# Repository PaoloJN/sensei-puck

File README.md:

# Sensei Puck

**Archived 2026-10-24. Never built.** This is the record of a college
proof-of-concept that got as far as a finished schematic, a mostly routed
4-layer PCB and a bring-up firmware variant, then stopped before the first
board order. It is kept public as a design record, not as a kit to build.

## What it was supposed to be

A Ø46 mm disc you drop into a glass or plastic jug. It sits on the bottom,
fully submerged, and logs what happens to the water: conductivity, temperature,
pressure (fill level and movement), a small spectral sensor with white / IR / UV
illumination, a capacitive wetness pair and a microphone. An nRF52840 module
talks BLE to a phone, radiating down through the container base from a dry air
cavity. Clear epoxy dip for waterproofing, magnetic pads for charging, OTA DFU
as the only reflash path after the dip. Raw counts plus acquisition settings
are stored; calibration happens downstream.

It was never meant to assess whether water is safe to drink. The honest scope
was "has this water changed since I last looked, and roughly how".

## What exists

| Part | State |
|---|---|
| `hardware/sensei-puck/` | KiCad 10 project. Schematic complete, ERC clean. Board placed on both faces (139 footprints, 4 layers). Last check: 1 clearance error, 25 connections still unrouted around the module. |
| `hardware/board-spec.md` | Pin contract, power rules, sensor notes, release requirements. |
| `firmware/` | PlatformIO + Adafruit nRF52 core. Custom `mdbt50q_puck` board and variant, safe-start `initVariant()`, REGOUT0 guard, a commissioning idle image and XIAO bench sketches. All targets compile. Nothing was ever flashed to a carrier. |
| `docs/images/` | Board renders, concept render, app mock (see the gallery below). |

Key parts: Raytac MDBT50Q-1MV2 (nRF52840), MCP73832 charger, TPS61023 5 V
boost for a 12-LED ring, FDC1004 capacitance, MS5837 pressure, AS7341 spectral,
LSM6DSO IMU, IM69D130 PDM mic, DS18B20U+ temperature, gold ENIG electrodes for
a 4-wire AC conductivity cell driven straight from GPIO with two-resistor
auto-ranging.

## Why it stopped

None of these alone killed it. Together they did.

- **A sealed puck is unforgiving.** Epoxy dip means no repair and no SWD after
  sealing, so the custom bootloader and the OTA path had to be proven perfect
  before the first dip. On a ~$300 budget with two PCB spins, one mistake in
  the pin map or the charger ends the project.
- **Radio through water was an unverified bet.** 2.4 GHz does not go through
  water. The plan relied on an air cavity under the board and the container
  base being thin glass or plastic, with store-and-forward and a tilt-triggered
  sync to cover the gaps. Plausible on paper, never measured, and it rules out
  metal bottles and thick ceramics outright.
- **The layout never closed.** The 0.4 mm pad pitch on the module, the no-via
  zone under the capacitive electrodes and the antenna keep-out box the module
  in on a 46 mm disc. Five autorouting strategies, two pin-swap passes and a
  0.1 mm local rule area got it from 130 opens to 25. The rest needed a
  placement redesign or a third attempt.
- **Every number needs a reference.** Conductivity and temperature readings
  only mean something against KCl standards or a lab meter. That is a bench
  campaign the project did not have time or access for.
- **The market check.** Products like WaterH (sensor in its own bottle) and the
  pool floats already ship the idea where it works, by owning the container.
  A drop-in puck for any container is the hard version, and the gap in the
  market is smaller than it looked.

## What I'd keep from it

The symmetric sensor face with the electrodes as the visual, the
GPIO-driven AC conductivity cell with switched bias, the "store raw counts and
settings" rule, and the habit of writing down every decision with a date and a
reason. The full decision log, work log, research notes and the earlier v1
board are in the git history before the archive commit.

## Gallery

## Running the firmware

```sh
cd firmware
pio run -e mdbt50q_puck -e puck
```

`mdbt50q_puck` is the carrier target. `puck` and `bench_*` run on a Seeed XIAO
nRF52840 Sense, which was the bench mule. See `firmware/README.md`.

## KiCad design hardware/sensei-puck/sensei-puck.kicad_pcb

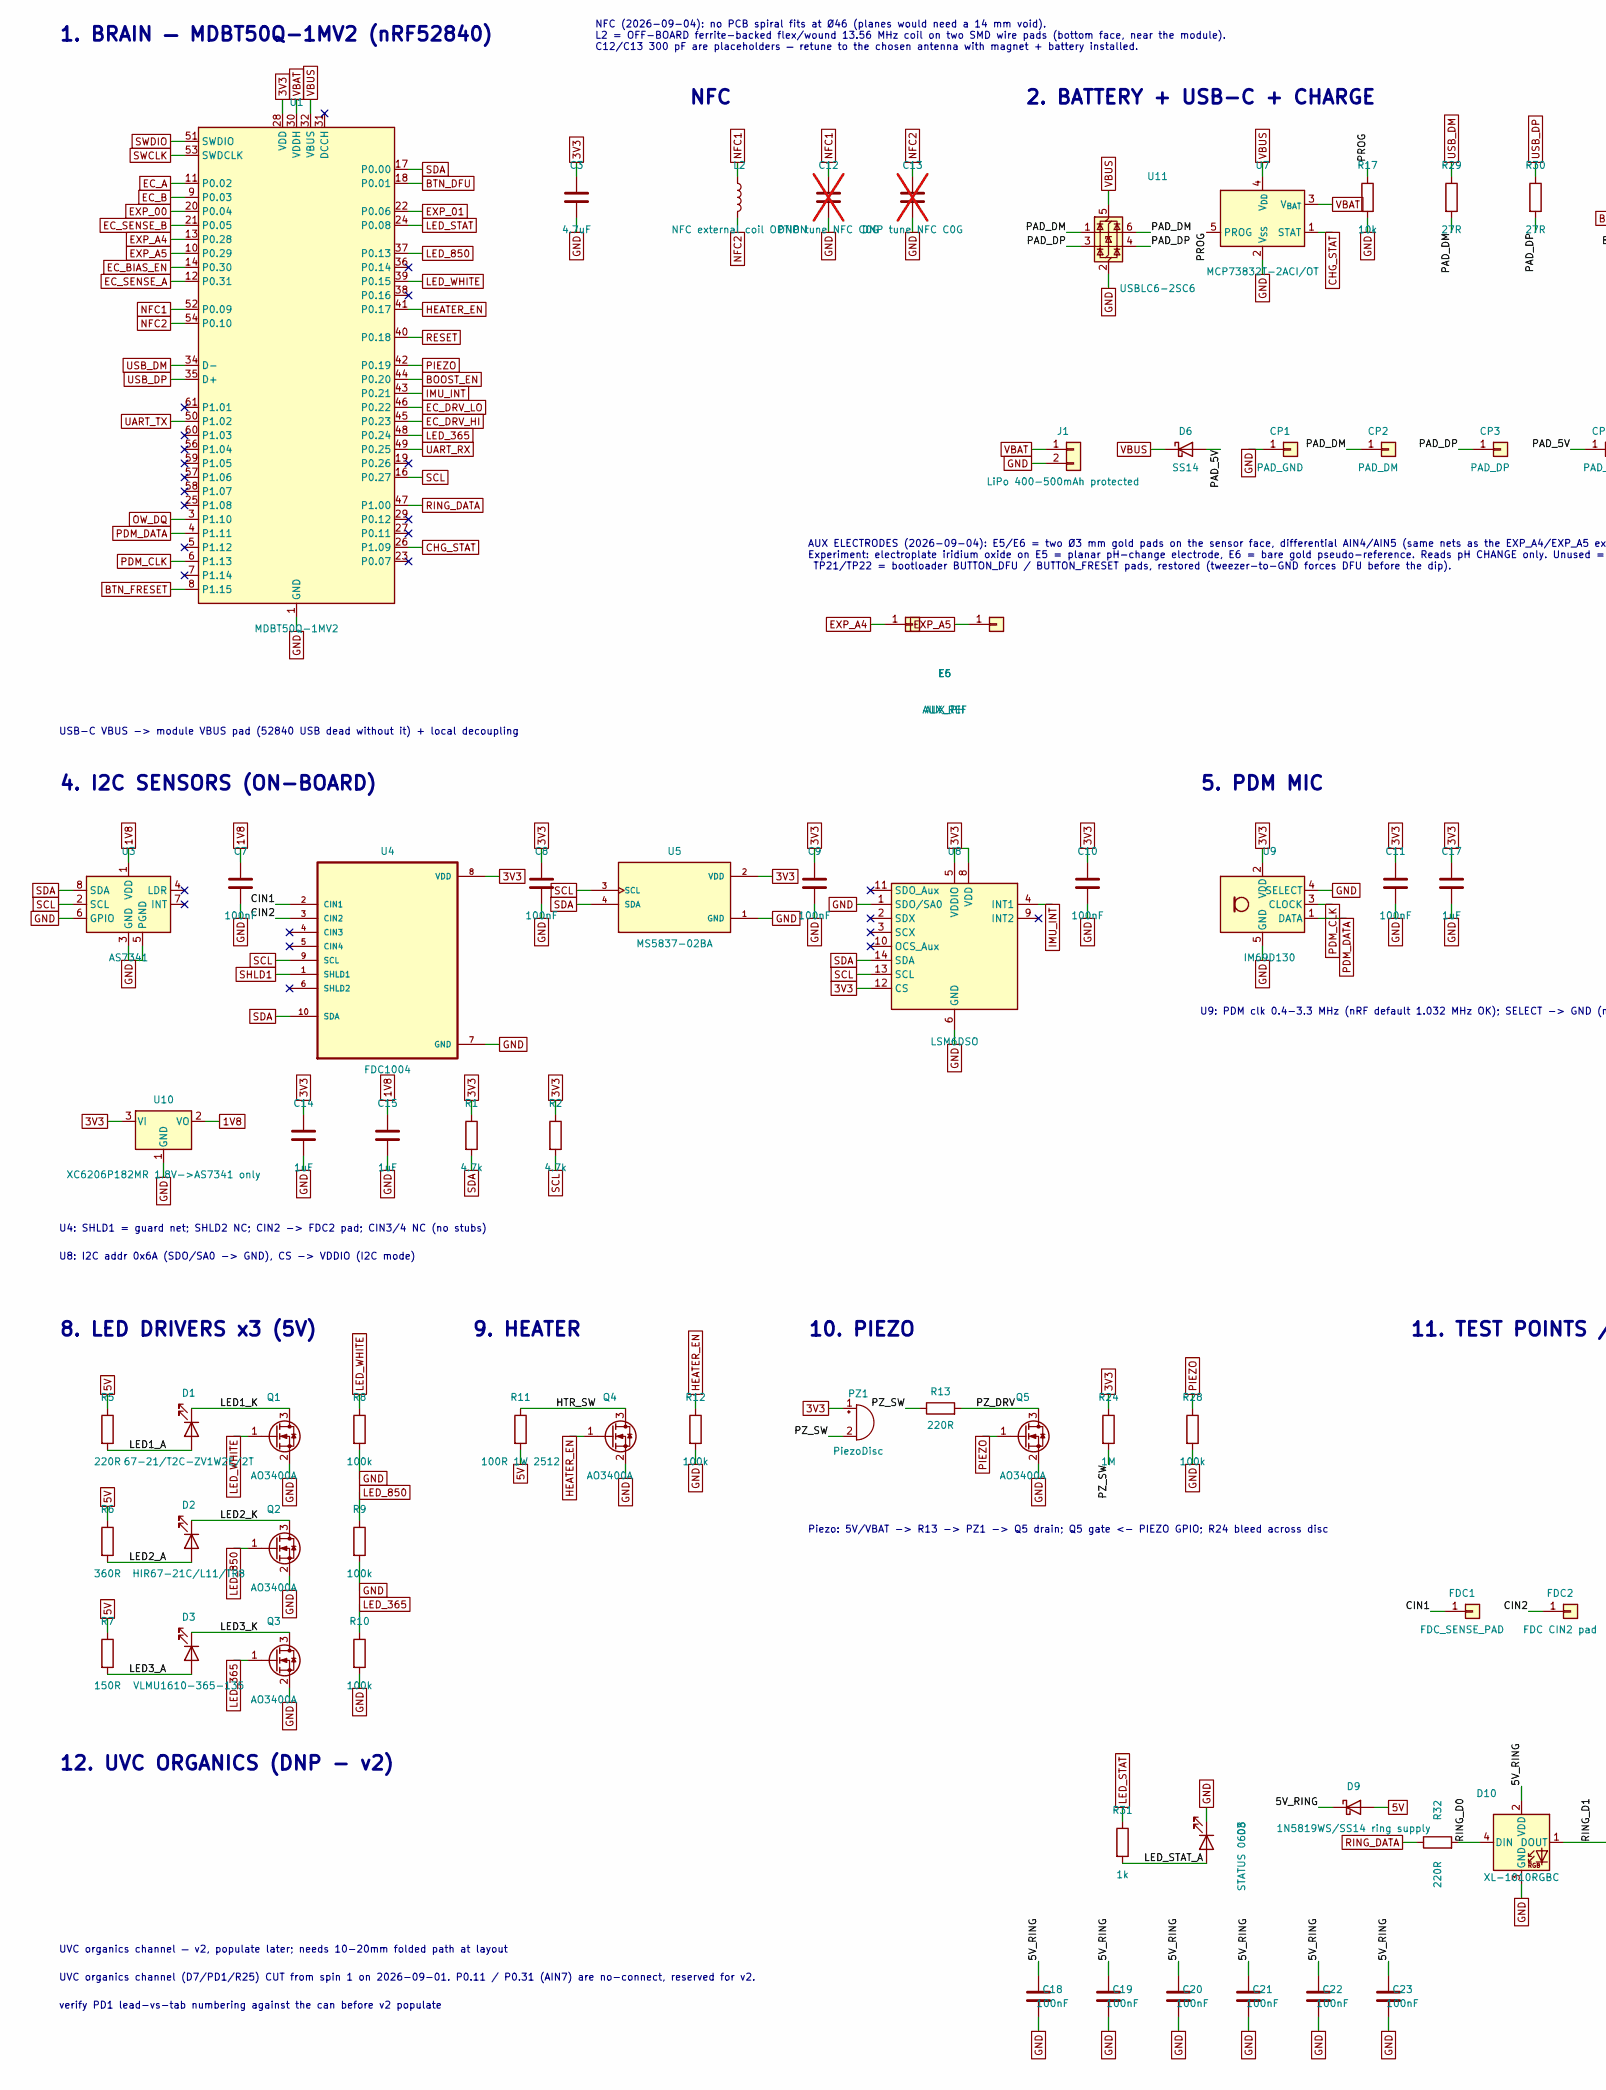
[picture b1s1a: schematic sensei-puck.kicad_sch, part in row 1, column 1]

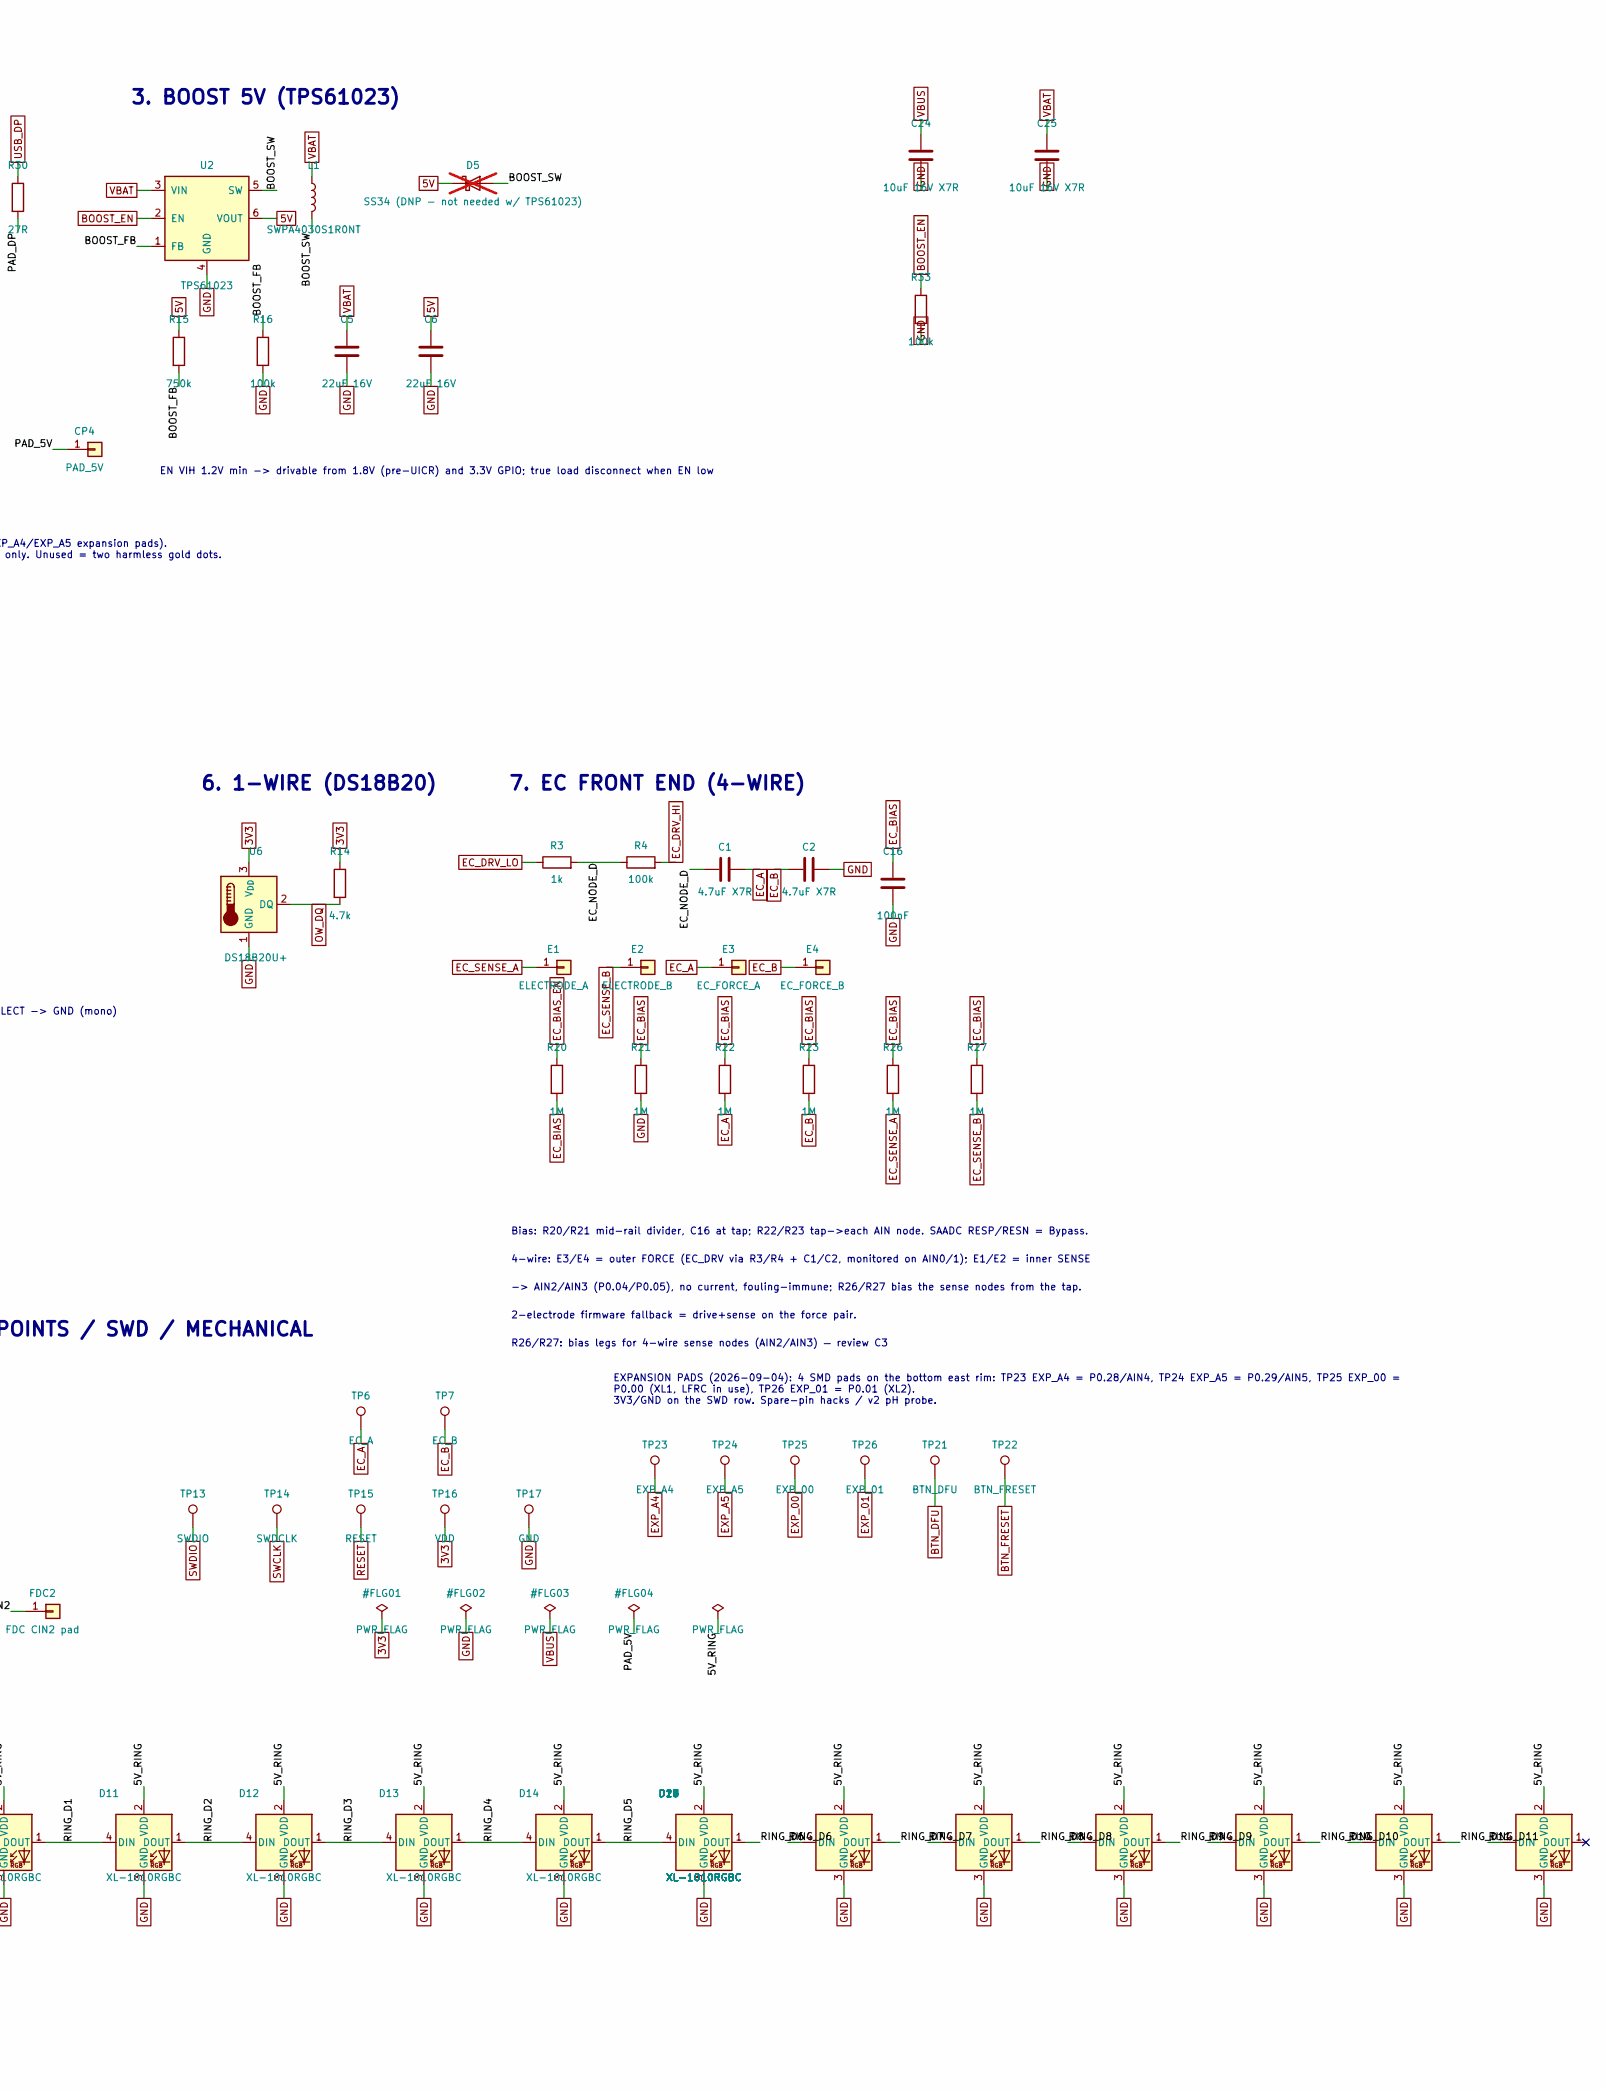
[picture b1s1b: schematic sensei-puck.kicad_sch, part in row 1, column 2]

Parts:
C1, C2: 4.7uF X7R; C_0805_2012Metric_Pad1.18x1.45mm_HandSolder
C3: 4.7uF; C_0805_2012Metric
C5, C6: 22uF 16V; C_0805_2012Metric_Pad1.18x1.45mm_HandSolder
C7, C8, C9, C10, C11, C16, C18, C19, C20, C21, C22, C23: 100nF; C_0402_1005Metric
C12, C13: DNP tune NFC C0G; C_0402_1005Metric; not fitted
C14, C15, C17: 1uF; C_0402_1005Metric
C24, C25: 10uF 16V X7R; C_1206_3216Metric
CP1: PAD_GND; CHG_Pad_D2.0mm
CP2: PAD_DM; CHG_Pad_D2.0mm
CP3: PAD_DP; CHG_Pad_D2.0mm
CP4: PAD_5V; CHG_Pad_D2.0mm
D1: 67-21/T2C-ZV1W2E/2T; LED_Everlight_67-21_PLCC2
D2: HIR67-21C/L11/TR8; LED_Everlight_67-21_PLCC2
D3: VLMU1610-365-135; LED_Vishay_VLMU1610
D5: SS34 (DNP - not needed w/ TPS61023); D_SMA; not fitted
D6: SS14; D_SOD-123
D8: STATUS 0603; LED_0603_1608Metric
D9: 1N5819WS/SS14 ring supply; D_SOD-123
D10, D11, D12, D13, D14, D15, D16, D17, D18, D19, D20, D21: XL-1010RGBC; LED_XL-1010RGBC
E1: ELECTRODE_A; EC_Electrode_2x8mm
E2: ELECTRODE_B; EC_Electrode_2x8mm
E3: EC_FORCE_A; EC_Electrode_2x8mm
E4: EC_FORCE_B; EC_Electrode_2x8mm
E5: AUX_PH; AUX_Pad_D3.0mm
E6: AUX_REF; AUX_Pad_D3.0mm
FDC1: FDC_SENSE_PAD; FDC_Sense_Pad_D7.9mm
FDC2: FDC CIN2 pad; FDC_Sense_Ring_D10-12.8mm
J1: LiPo 400-500mAh protected; JST_PH_S2B-PH-K_1x02_P2.00mm_Horizontal
L1: SWPA4030S1R0NT; L_Sunlord_SWPA4030S
L2: NFC external coil OPTION; WirePad_1x02_SMD_1.5x3mm
PZ1: PiezoDisc; PZ_WirePad_1x02_SMD
Q1, Q2, Q3, Q4, Q5: AO3400A; SOT-23
R1, R2, R14: 4.7k; R_0402_1005Metric
R3, R31: 1k; R_0402_1005Metric
R4, R8, R9, R10, R12, R16, R28, R33: 100k; R_0402_1005Metric
R5, R13, R32: 220R; R_0402_1005Metric
R6: 360R; R_0402_1005Metric
R7: 150R; R_0402_1005Metric
R11: 100R 1W 2512; R_2512_6332Metric_Pad1.40x3.35mm_HandSolder
R15: 750k; R_0402_1005Metric
R17: 10k; R_0402_1005Metric
R20, R21, R22, R23, R24, R26, R27: 1M; R_0402_1005Metric
R29, R30: 27R; R_0402_1005Metric
TP6: EC_A; TestPoint_Pad_D1.5mm
TP7: EC_B; TestPoint_Pad_D1.5mm
TP13: SWDIO; TestPoint_Pad_D1.5mm
TP14: SWDCLK; TestPoint_Pad_D1.5mm
TP15: RESET; TestPoint_Pad_D1.5mm
TP16: VDD; TestPoint_Pad_D1.5mm
TP17: GND; TestPoint_Pad_D1.5mm
TP21: BTN_DFU; ExpPad_1.2x2.2mm
TP22: BTN_FRESET; ExpPad_1.2x2.2mm
TP23: EXP_A4; ExpPad_1.2x2.2mm
TP24: EXP_A5; ExpPad_1.2x2.2mm
TP25: EXP_00; ExpPad_1.2x2.2mm
TP26: EXP_01; ExpPad_1.2x2.2mm
U1: MDBT50Q-1MV2
U2: TPS61023; SOT-563
U3: AS7341; AMS_OLGA-8_2x3.1mm_P0.8mm
U4: FDC1004; SOP50P490X110-10N
U5: MS5837-02BA; XDCR_MS583702BA01-50
U6: DS18B20U+; DS18B20U_MSOP8
U7: MCP73832T-2ACI/OT; SOT-23-5
U8: LSM6DSO; LGA-14_3x2.5mm_P0.5mm_LayoutBorder3x4y
U9: IM69D130; Infineon_PG-LLGA-5-1
U10: XC6206P182MR 1.8V->AS7341 only; SOT-23
U11: USBLC6-2SC6; SOT-23-6

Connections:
1V8: C7.1, C15.1, U3.1 (VDD), U10.2 (VO)
3V3: C3.1, C8.1, C9.1, C10.1, C11.1, C14.1, C17.1, PZ1.1 (+), R1.1, R2.1, R14.1, R24.1, TP16.1 (1_1), U1.28 (VDD), U4.8 (VDD), U5.2 (VDD), U6.3 (V_{DD}), U8.5 (VDDIO), U8.8 (VDD), U8.12 (CS), U9.2 (VDD), U10.3 (VI)
5V: C6.1, D5.1 (K), D9.2 (A), R5.1, R6.1, R7.1, R11.2, R15.1, U2.6 (VOUT)
/5V_RING: C18.1, C19.1, C20.1, C21.1, C22.1, C23.1, D9.1 (K), D10.2 (VDD), D11.2 (VDD), D12.2 (VDD), D13.2 (VDD), D14.2 (VDD), D15.2 (VDD), D16.2 (VDD), D17.2 (VDD), D18.2 (VDD), D19.2 (VDD), D20.2 (VDD), D21.2 (VDD)
/BOOST_FB: R15.2, R16.1, U2.1 (FB)
/BOOST_SW: D5.2 (A), L1.2, U2.5 (SW)
/CIN1: FDC1.1 (Pin_1_1), U4.2 (CIN1)
/CIN2: FDC2.1 (Pin_1_1), U4.3 (CIN2)
/EC_NODE_D: C1.1, R3.2, R4.1
/HTR_SW: Q4.3 (D), R11.1
/LED1_A: D1.2 (A), R5.2
/LED1_K: D1.1 (K), Q1.3 (D)
/LED2_A: D2.2 (A), R6.2
/LED2_K: D2.1 (K), Q2.3 (D)
/LED3_A: D3.2 (A), R7.2
/LED3_K: D3.1 (K), Q3.3 (D)
/LED_STAT_A: D8.2 (A), R31.2
/PAD_5V: CP4.1 (Pin_1_1), D6.2 (A)
/PAD_DM: CP2.1 (Pin_1_1), R29.2, U11.1 (I/O1), U11.6 (I/O1)
/PAD_DP: CP3.1 (Pin_1_1), R30.2, U11.3 (I/O2), U11.4 (I/O2)
/PROG: R17.1, U7.5 (PROG)
/PZ_DRV: Q5.3 (D), R13.2
/PZ_SW: PZ1.2 (-), R13.1, R24.2
/RING_D0: D10.4 (DIN), R32.2
/RING_D1: D10.1 (DOUT), D11.4 (DIN)
/RING_D2: D11.1 (DOUT), D12.4 (DIN)
/RING_D3: D12.1 (DOUT), D13.4 (DIN)
/RING_D4: D13.1 (DOUT), D14.4 (DIN)
/RING_D5: D14.1 (DOUT), D15.4 (DIN)
/RING_D6: D15.1 (DOUT), D16.4 (DIN)
/RING_D7: D16.1 (DOUT), D17.4 (DIN)
/RING_D8: D17.1 (DOUT), D18.4 (DIN)
/RING_D9: D18.1 (DOUT), D19.4 (DIN)
/RING_D10: D19.1 (DOUT), D20.4 (DIN)
/RING_D11: D20.1 (DOUT), D21.4 (DIN)
BOOST_EN: R33.1, U1.44 (P0.20), U2.2 (EN)
BTN_DFU: TP21.1 (1_1), U1.18 (P0.01)
BTN_FRESET: TP22.1 (1_1), U1.8 (P1.15)
CHG_STAT: U1.26 (P1.09), U7.1 (STAT)
EC_A: C1.2, E3.1 (Pin_1_1), R22.2, TP6.1 (1_1), U1.11 (P0.02)
EC_B: C2.1, E4.1 (Pin_1_1), R23.2, TP7.1 (1_1), U1.9 (P0.03)
EC_BIAS: C16.1, R20.2, R21.1, R22.1, R23.1, R26.1, R27.1
EC_BIAS_EN: R20.1, U1.14 (P0.30)
EC_DRV_HI: R4.2, U1.45 (P0.23)
EC_DRV_LO: R3.1, U1.46 (P0.22)
EC_SENSE_A: E1.1 (Pin_1_1), R26.2, U1.12 (P0.31)
EC_SENSE_B: E2.1 (Pin_1_1), R27.2, U1.21 (P0.05)
EXP_00: TP25.1, U1.20 (P0.04)
EXP_01: TP26.1, U1.22 (P0.06)
EXP_A4: E5.1 (Pin_1_1), TP23.1, U1.13 (P0.28)
EXP_A5: E6.1 (Pin_1_1), TP24.1, U1.10 (P0.29)
GND: C2.2, C3.2, C5.2, C6.2, C7.2, C8.2, C9.2, C10.2, C11.2, C12.2, C13.2, C14.2, C15.2, C16.2, C17.2, C18.2, C19.2, C20.2, C21.2, C22.2, C23.2, C24.2, C25.2, CP1.1 (Pin_1_1), D8.1 (K), D10.3 (GND), D11.3 (GND), D12.3 (GND), D13.3 (GND), D14.3 (GND), D15.3 (GND), D16.3 (GND), D17.3 (GND), D18.3 (GND), D19.3 (GND), D20.3 (GND), D21.3 (GND), J1.2, Q1.2 (S), Q2.2 (S), Q3.2 (S), Q4.2 (S), Q5.2 (S), R8.2, R9.2, R10.2, R12.2, R16.2, R17.2, R21.2, R28.2, R33.2, TP17.1 (1_1), U1.1 (GND), U1.2 (GND), U1.15 (GND), U1.33 (GND), U1.55 (GND), U2.4 (GND), U3.3 (GND), U3.5 (PGND), U3.6 (GPIO), U4.7 (GND), U5.1 (GND), U6.1 (GND), U7.2 (V_{SS}), U8.1 (SDO/SA0), U8.6 (GND), U8.7 (GND), U9.4 (SELECT), U9.5 (GND), U10.1 (GND), U11.2 (GND)
HEATER_EN: Q4.1 (G), R12.1, U1.41 (P0.17)
IMU_INT: U1.43 (P0.21), U8.4 (INT1)
LED_365: Q3.1 (G), R10.1, U1.48 (P0.24)
LED_850: Q2.1 (G), R9.1, U1.37 (P0.13)
LED_STAT: R31.1, U1.24 (P0.08)
LED_WHITE: Q1.1 (G), R8.1, U1.39 (P0.15)
NFC1: C12.1, L2.1, U1.52 (P0.09)
NFC2: C13.1, L2.2, U1.54 (P0.10)
OW_DQ: R14.2, U1.3 (P1.10), U6.2 (DQ)
PDM_CLK: U1.6 (P1.13), U9.3 (CLOCK)
PDM_DATA: U1.4 (P1.11), U9.1 (DATA)
PIEZO: Q5.1 (G), R28.1, U1.42 (P0.19)
RESET: TP15.1 (1_1), U1.40 (P0.18)
RING_DATA: R32.1, U1.47 (P1.00)
SCL: R2.2, U1.16 (P0.27), U3.2 (SCL), U4.9 (SCL), U5.3 (SCL), U8.13 (SCL)
SDA: R1.2, U1.17 (P0.00), U3.8 (SDA), U4.10 (SDA), U5.4 (SDA), U8.14 (SDA)
SHLD1: U4.1 (SHLD1)
SWCLK: TP14.1 (1_1), U1.53 (SWDCLK)
SWDIO: TP13.1 (1_1), U1.51 (SWDIO)
UART_RX: U1.49 (P0.25)
UART_TX: U1.50 (P1.02)
USB_DM: R29.1, U1.34 (D-)
USB_DP: R30.1, U1.35 (D+)
VBAT: C5.1, C25.1, J1.1, L1.1, U1.30 (VDDH), U2.3 (VIN), U7.3 (V_{BAT})
VBUS: C24.1, D6.1 (K), U1.32 (VBUS), U7.4 (V_{DD}), U11.5 (VBUS)

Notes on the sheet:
7. EC FRONT END (4-WIRE)
9. HEATER
5. PDM MIC
-> AIN2/AIN3 (P0.04/P0.05), no current, fouling-immune; R26/R27 bias the sense nodes from the tap.
10. PIEZO
2-electrode firmware fallback = drive+sense on the force pair.
Bias: R20/R21 mid-rail divider, C16 at tap; R22/R23 tap->each AIN node. SAADC RESP/RESN = Bypass.
6. 1-WIRE (DS18B20)
verify PD1 lead-vs-tab numbering against the can before v2 populate
4. I2C SENSORS (ON-BOARD)
UVC organics channel (D7/PD1/R25) CUT from spin 1 on 2026-09-01. P0.11 / P0.31 (AIN7) are no-connect, reserved for v2.
NFC (2026-09-04): no PCB spiral fits at Ø46 (planes would need a 14 mm void). L2 = OFF-BOARD ferrite-backed flex/wound 13.56 MHz coil on two SMD wire pads (bottom face, near the module). C12/C13 300 pF are placeholders — retune to the chosen antenna with magnet + battery installed.
1. BRAIN — MDBT50Q-1MV2 (nRF52840)
UVC organics channel — v2, populate later; needs 10-20mm folded path at layout
NFC
R26/R27: bias legs for 4-wire sense nodes (AIN2/AIN3) — review C3
U8: I2C addr 0x6A (SDO/SA0 -> GND), CS -> VDDIO (I2C mode)
U9: PDM clk 0.4-3.3 MHz (nRF default 1.032 MHz OK); SELECT -> GND (mono)
EN VIH 1.2V min -> drivable from 1.8V (pre-UICR) and 3.3V GPIO; true load disconnect when EN low
AUX ELECTRODES (2026-09-04): E5/E6 = two Ø3 mm gold pads on the sensor face, differential AIN4/AIN5 (same nets as the EXP_A4/EXP_A5 expansion pads). Experiment: electroplate iridium oxide on E5 = planar pH-change electrode, E6 = bare gold pseudo-reference. Reads pH CHANGE only. Unused = two harmles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
8. LED DRIVERS x3 (5V)
USB-C VBUS -> module VBUS pad (52840 USB dead without it) + local decoupling
Piezo: 5V/VBAT -> R13 -> PZ1 -> Q5 drain; Q5 gate <- PIEZO GPIO; R24 bleed across disc
EXPANSION PADS (2026-09-04): 4 SMD pads on the bottom east rim: TP23 EXP_A4 = P0.28/AIN4, TP24 EXP_A5 = P0.29/AIN5, TP25 EXP_00 = P0.00 (XL1, LFRC in use), TP26 EXP_01 = P0.01 (XL2). 3V3/GND on the SWD row. Spare-pin hacks / v2 pH probe.
12. UVC ORGANICS (DNP - v2)
3. BOOST 5V (TPS61023)
4-wire: E3/E4 = outer FORCE (EC_DRV via R3/R4 + C1/C2, monitored on AIN0/1); E1/E2 = inner SENSE
2. BATTERY + USB-C + CHARGE
U4: SHLD1 = guard net; SHLD2 NC; CIN2 -> FDC2 pad; CIN3/4 NC (no stubs)
11. TEST POINTS / SWD / MECHANICAL

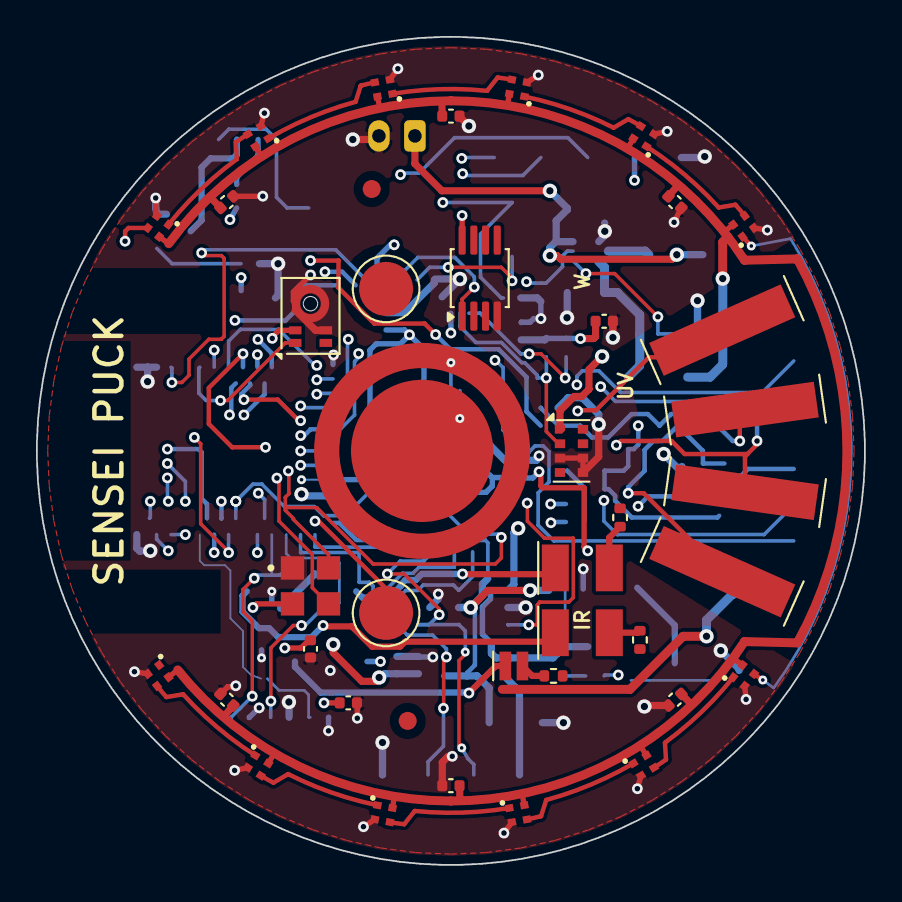
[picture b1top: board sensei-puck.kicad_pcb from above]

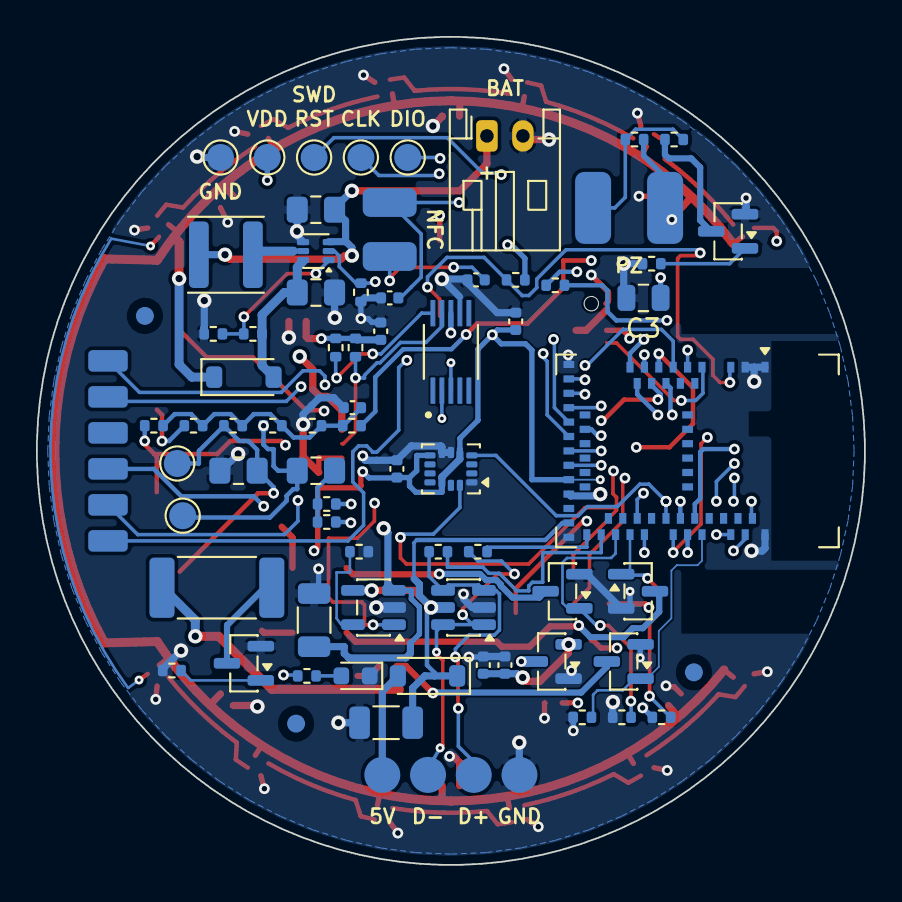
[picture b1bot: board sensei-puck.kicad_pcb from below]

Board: 4 copper layers, 46.0 x 46.0 mm, 122 parts (81 on the bottom side), 74 nets.

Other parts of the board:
FID3, FID4, FID5, FID6, FID7: FIDUCIAL; Fiducial_1mm_Mask2mm

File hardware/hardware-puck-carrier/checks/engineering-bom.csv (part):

Reference,Value,Footprint,Population
C1,4.7uF X7R,Capacitor_SMD:C_0805_2012Metric_Pad1.18x1.45mm_HandSolder,MPN/assembly quote review required
C10,100nF,Capacitor_SMD:C_0402_1005Metric,MPN/assembly quote review required
C11,100nF,Capacitor_SMD:C_0402_1005Metric,MPN/assembly quote review required
C12,DNP tune NFC C0G,Capacitor_SMD:C_0402_1005Metric,DNP
C13,DNP tune NFC C0G,Capacitor_SMD:C_0402_1005Metric,DNP
C14,1uF,Capacitor_SMD:C_0402_1005Metric,MPN/assembly quote review required
C15,1uF,Capacitor_SMD:C_0402_1005Metric,MPN/assembly quote review required
C16,100nF,Capacitor_SMD:C_0402_1005Metric,MPN/assembly quote review required
C17,1uF,Capacitor_SMD:C_0402_1005Metric,MPN/assembly quote review required
C18,100nF,Capacitor_SMD:C_0402_1005Metric,MPN/assembly quote review required
C19,100nF,Capacitor_SMD:C_0402_1005Metric,MPN/assembly quote review required
C2,4.7uF X7R,Capacitor_SMD:C_0805_2012Metric_Pad1.18x1.45mm_HandSolder,MPN/assembly quote review required
C20,100nF,Capacitor_SMD:C_0402_1005Metric,MPN/assembly quote review required
C21,100nF,Capacitor_SMD:C_0402_1005Metric,MPN/assembly quote review required
C22,100nF,Capacitor_SMD:C_0402_1005Metric,MPN/assembly quote review required
C23,100nF,Capacitor_SMD:C_0402_1005Metric,MPN/assembly quote review required
C24,10uF 16V X7R,Capacitor_SMD:C_1206_3216Metric,MPN/assembly quote review required
C25,10uF 16V X7R,Capacitor_SMD:C_1206_3216Metric,MPN/assembly quote review required
C3,100uF,Capacitor_SMD:C_1210_3225Metric_Pad1.33x2.70mm_HandSolder,MPN/assembly quote review required
C5,22uF 16V,Capacitor_SMD:C_0805_2012Metric_Pad1.18x1.45mm_HandSolder,MPN/assembly quote review required
C6,22uF 16V,Capacitor_SMD:C_0805_2012Metric_Pad1.18x1.45mm_HandSolder,MPN/assembly quote review required
C7,100nF,Capacitor_SMD:C_0402_1005Metric,MPN/assembly quote review required
C8,100nF,Capacitor_SMD:C_0402_1005Metric,MPN/assembly quote review required
C9,100nF,Capacitor_SMD:C_0402_1005Metric,MPN/assembly quote review required
CP1,PAD_GND,puck:CHG_Pad_D2.0mm,PCB feature
CP2,PAD_DM,puck:CHG_Pad_D2.0mm,PCB feature
CP3,PAD_DP,puck:CHG_Pad_D2.0mm,PCB feature
CP4,PAD_5V,puck:CHG_Pad_D2.0mm,PCB feature
D1,67-21/T2C-ZV1W2E/2T,puck:LED_Everlight_67-21_PLCC2,MPN/assembly quote review required
D10,XL-1010RGBC,puck:LED_XL-1010RGBC,MPN/assembly quote review required
D11,XL-1010RGBC,puck:LED_XL-1010RGBC,MPN/assembly quote review required
D12,XL-1010RGBC,puck:LED_XL-1010RGBC,MPN/assembly quote review required
D13,XL-1010RGBC,puck:LED_XL-1010RGBC,MPN/assembly quote review required
D14,XL-1010RGBC,puck:LED_XL-1010RGBC,MPN/assembly quote review required
D15,XL-1010RGBC,puck:LED_XL-1010RGBC,MPN/assembly quote review required
D16,XL-1010RGBC,puck:LED_XL-1010RGBC,MPN/assembly quote review required
D17,XL-1010RGBC,puck:LED_XL-1010RGBC,MPN/assembly quote review required
D18,XL-1010RGBC,puck:LED_XL-1010RGBC,MPN/assembly quote review required
D19,XL-1010RGBC,puck:LED_XL-1010RGBC,MPN/assembly quote review required
D2,HIR67-21C/L11/TR8,puck:LED_Everlight_67-21_PLCC2,MPN/assembly quote review required
D20,XL-1010RGBC,puck:LED_XL-1010RGBC,MPN/assembly quote review required
D21,XL-1010RGBC,puck:LED_XL-1010RGBC,MPN/assembly quote review required
D3,VLMU1610-365-135,puck:LED_Vishay_VLMU1610,MPN/assembly quote review required
D6,SS14,Diode_SMD:D_SOD-123,MPN/assembly quote review required
D8,STATUS 0603,LED_SMD:LED_0603_1608Metric,MPN/assembly quote review required
D9,1N5819WS/SS14 ring supply,Diode_SMD:D_SOD-123,MPN/assembly quote review required
E1,ELECTRODE_A,puck:EC_Electrode_2x8mm,PCB feature
E2,ELECTRODE_B,puck:EC_Electrode_2x8mm,PCB feature
E3,EC_FORCE_A,puck:EC_Electrode_2x8mm,PCB feature
E4,EC_FORCE_B,puck:EC_Electrode_2x8mm,PCB feature
E5,AUX_PH,puck:AUX_Pad_D3.0mm,PCB feature
E6,AUX_REF,puck:AUX_Pad_D3.0mm,PCB feature
FDC1,FDC_SENSE_PAD,puck:FDC_Sense_Pad_D7.9mm,PCB feature
FDC2,FDC CIN2 pad,puck:FDC_Sense_Ring_D10-12.8mm,PCB feature
J1,LiPo 400-500mAh protected,Connector_JST:JST_PH_S2B-PH-K_1x02_P2.00mm_Horizontal,MPN/assembly quote review required
L1,SWPA4030S1R0NT,Inductor_SMD:L_Sunlord_SWPA4030S,MPN/assembly quote review required
L2,NFC external coil OPTION,puck:WirePad_1x02_SMD_1.5x3mm,MPN/assembly quote review required
PZ1,PiezoDisc,puck:PZ_WirePad_1x02_SMD,MPN/assembly quote review required
Q1,AO3400A,Package_TO_SOT_SMD:SOT-23,MPN/assembly quote review required
Q2,AO3400A,Package_TO_SOT_SMD:SOT-23,MPN/assembly quote review required
Q3,AO3400A,Package_TO_SOT_SMD:SOT-23,MPN/assembly quote review required
Q4,AO3400A,Package_TO_SOT_SMD:SOT-23,MPN/assembly quote review required
Q5,AO3400A,Package_TO_SOT_SMD:SOT-23,MPN/assembly quote review required
R1,4.7k,Resistor_SMD:R_0402_1005Metric,MPN/assembly quote review required
R10,100k,Resistor_SMD:R_0402_1005Metric,MPN/assembly quote review required
R11,100R 1W 2512,Resistor_SMD:R_2512_6332Metric_Pad1.40x3.35mm_HandSolder,MPN/assembly quote review required
R12,100k,Resistor_SMD:R_0402_1005Metric,MPN/assembly quote review required
R13,220R,Resistor_SMD:R_0402_1005Metric,MPN/assembly quote review required
R14,4.7k,Resistor_SMD:R_0402_1005Metric,MPN/assembly quote review required
R15,750k,Resistor_SMD:R_0402_1005Metric,MPN/assembly quote review required
R16,100k,Resistor_SMD:R_0402_1005Metric,MPN/assembly quote review required
R17,10k,Resistor_SMD:R_0402_1005Metric,MPN/assembly quote review required
R2,4.7k,Resistor_SMD:R_0402_1005Metric,MPN/assembly quote review required
R20,1M,Resistor_SMD:R_0402_1005Metric,MPN/assembly quote review required
R21,1M,Resistor_SMD:R_0402_1005Metric,MPN/assembly quote review required
R22,1M,Resistor_SMD:R_0402_1005Metric,MPN/assembly quote review required
R23,1M,Resistor_SMD:R_0402_1005Metric,MPN/assembly quote review required
R24,1M,Resistor_SMD:R_0402_1005Metric,MPN/assembly quote review required
R26,1M,Resistor_SMD:R_0402_1005Metric,MPN/assembly quote review required
R27,1M,Resistor_SMD:R_0402_1005Metric,MPN/assembly quote review required
R28,100k,Resistor_SMD:R_0402_1005Metric,MPN/assembly quote review required
R29,27R,Resistor_SMD:R_0402_1005Metric,MPN/assembly quote review required
R3,1k,Resistor_SMD:R_0402_1005Metric,MPN/assembly quote review required
R30,27R,Resistor_SMD:R_0402_1005Metric,MPN/assembly quote review required
R31,1k,Resistor_SMD:R_0402_1005Metric,MPN/assembly quote review required
R32,220R,Resistor_SMD:R_0402_1005Metric,MPN/assembly quote review required
R33,100k,Resistor_SMD:R_0402_1005Metric,MPN/assembly quote review required
R4,100k,Resistor_SMD:R_0402_1005Metric,MPN/assembly quote review required
R5,220R,Resistor_SMD:R_0402_1005Metric,MPN/assembly quote review required
R6,360R,Resistor_SMD:R_0402_1005Metric,MPN/assembly quote review required
R7,150R,Resistor_SMD:R_0402_1005Metric,MPN/assembly quote review required
R8,100k,Resistor_SMD:R_0402_1005Metric,MPN/assembly quote review required
R9,100k,Resistor_SMD:R_0402_1005Metric,MPN/assembly quote review required
TP13,SWDIO,TestPoint:TestPoint_Pad_D1.5mm,PCB feature
TP14,SWDCLK,TestPoint:TestPoint_Pad_D1.5mm,PCB feature
TP15,RESET,TestPoint:TestPoint_Pad_D1.5mm,PCB feature
TP16,VDD,TestPoint:TestPoint_Pad_D1.5mm,PCB feature
TP17,GND,TestPoint:TestPoint_Pad_D1.5mm,PCB feature
TP21,BTN_DFU,puck:ExpPad_1.2x2.2mm,PCB feature
TP22,BTN_FRESET,puck:ExpPad_1.2x2.2mm,PCB feature
TP23,EXP_A4,puck:ExpPad_1.2x2.2mm,PCB feature
TP24,EXP_A5,puck:ExpPad_1.2x2.2mm,PCB feature
TP25,EXP_00,puck:ExpPad_1.2x2.2mm,PCB feature
TP26,EXP_01,puck:ExpPad_1.2x2.2mm,PCB feature
TP6,EC_A,TestPoint:TestPoint_Pad_D1.5mm,PCB feature
TP7,EC_B,TestPoint:TestPoint_Pad_D1.5mm,PCB feature
U1,MDBT50Q-1MV2,puck:MDBT50Q-1MV2,MPN/assembly quote review required
U10,XC6206P182MR 1.8V->AS7341 only,Package_TO_SOT_SMD:SOT-23,MPN/assembly quote review required
U11,USBLC6-2SC6,Package_TO_SOT_SMD:SOT-23-6,MPN/assembly quote review required
U2,TPS61023,Package_TO_SOT_SMD:SOT-563,MPN/assembly quote review required
U3,AS7341,puck:AMS_OLGA-8_2x3.1mm_P0.8mm,MPN/assembly quote review required
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
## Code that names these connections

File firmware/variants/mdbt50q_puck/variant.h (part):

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 * Bootloader buttons — picked 2026-08-31 (was "revisit at bootloader-pick
 * time"): BUTTON_DFU = P1.08 (TP21), BUTTON_FRESET = P1.09 (TP22). Bare
 * exposed pads, tweezer-to-GND with internal pull-ups; both pass the
 * button-pin blacklist (not IMU_INT, not PDM, not externally driven). The
 * bootloader board.h must use these same numbers.
 */
#define PIN_LED1             (8)    // P0.08 (module pad 24) — D8 status LED, net LED_STAT; moved from P0.12 (2026-10-16 pass 2)
#define LED_BUILTIN          PIN_LED1
#define LED_CONN             PIN_LED1
#define LED_RED              PIN_LED1
#define LED_BLUE             PIN_LED1
#define LED_STATE_ON         (1)    // active high (drives D8 through R31)

#define PIN_BTN_DFU          (1)   // P0.01 (module pad 18) — TP21, tweezer-to-GND forces DFU; pass 3
#define PIN_BTN_FRESET       (47)   // P1.15 (module pad 8) — TP22, factory-reset button pad; moved from P1.09 for routing (2026-10-16)

// Expansion pads (bottom east rim, 2026-09-04): spare pins on 4 SMD pads. 3V3/GND on the SWD row.
#define PIN_EXP_A4      (28)   // P0.28 / AIN4 — TP23 (v2 pH probe candidate)
#define PIN_EXP_A5      (29)   // P0.29 / AIN5 — TP24
#define PIN_EXP_00           (4)   // P0.04 (module pad 20) — TP25; pass 3
#define PIN_EXP_01           (6)   // P0.06 (module pad 22) — TP26; pass 3

/*
 * Analog pins — SAADC channel order (AIN0..AIN7)
 */
#define PIN_A0               (2)    // P0.02 AIN0 = EC_A
#define PIN_A1               (3)    // P0.03 AIN1 = EC_B
#define PIN_A2               (4)    // P0.04 AIN2 = EXP_00 (digital) since the 2026-10-16 pin passes
#define PIN_A3               (5)    // P0.05 AIN3 = EC_SENSE_B
#define PIN_A4               (28)   // P0.28 AIN4 — EXP_A4 pad TP23 (spare, freed by EC-drive move)
#define PIN_A5               (29)   // P0.29 AIN5 — spare (freed by EC-drive move)
#define PIN_A6               (30)   // P0.30 AIN6 — EC_BIAS_EN (slow GPIO)
#define PIN_A7               (31)   // P0.31 AIN7 = EC_SENSE_A (since the 2026-10-16 pin swap)

static const uint8_t A0  = PIN_A0 ;
static const uint8_t A1  = PIN_A1 ;
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 *----------------------------------------------------------------------------*/

// EC front end — 4-electrode cell
#define PIN_EC_A             (2)    // P0.02 AIN0 — force node E3 (2-el. fallback)
#define PIN_EC_B             (3)    // P0.03 AIN1 — force node E4 (2-el. fallback)
#define PIN_EC_SENSE_A       (31)   // P0.31 AIN7 (module pad 12) — inner sense electrode E1 (4-wire); moved from P0.04 for routing (2026-10-16)
#define PIN_EC_SENSE_B       (5)    // P0.05 AIN3 — inner sense electrode E2 (4-wire)
#define PIN_EC_DRV_LO        (22)   // P0.22 — 1 kOhm range drive (H0H1 high-drive)
#define PIN_EC_DRV_HI        (23)   // P0.23 — 100 kOhm range drive (H0H1 high-drive)
#define PIN_EC_BIAS_EN       (30)   // P0.30 — R20 divider feed; LOW between acquisitions
#define PIN_RING_DATA       (32)   // P1.00 — XL-1010 ring; LOW while boost is off

// Illumination FET gates (loads on 5 V boost rail)
#define PIN_LED_WHITE        (15)   // P0.15 (module pad 39) — Q1 gate; pin pass 4 (2026-10-17), was P0.13
#define PIN_LED_850          (13)   // P0.13 (module pad 37) — Q2 gate (850 nm scatter turbidity); pin pass 4 (2026-10-17), was P1.02
#define PIN_LED_365          (24)   // P0.24 (module pad 48) — Q3 gate (365 nm); pin pass 4 (2026-10-17), was P0.15

// Misc peripherals
#define PIN_OW_DQ            (42)   // P1.10 (module pad 3) — DS18B20U+ 1-wire; moved from P0.16 (2026-10-16 pass 2)
#define PIN_HEATER_EN        (17)   // P0.17 — Q4 gate
#define PIN_PIEZO            (19)   // P0.19 — Q5 gate (low-side FET, load off GPIO)
#define PIN_BOOST_EN         (20)   // P0.20 — TPS61023 EN
#define PIN_IMU_INT          (21)   // P0.21 — LSM6DSO INT1 (tilt wake)
#define PIN_CHG_STAT         (41)   // P1.09 (module pad 26) — MCP73832 STAT; pass 3

// PDM microphone (IM69D130) — names the core PDM library expects, plus the
// spec's PIN_PDM_DATA alias
#define PIN_PDM_CLK          (45)   // P1.13 (module pad 6); moved from P0.08 for routing (2026-10-16)
#define PIN_PDM_DATA         (43)   // P1.11 (module pad 4); moved from P0.06 for routing (2026-10-16)
#define PIN_PDM_DIN          PIN_PDM_DATA
#define PIN_PDM_PWR          (-1)   // mic powered from rail, no power gate

// Debug UART aliases (test points only; wired into Serial1 above)
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
// NFC coil — RESERVED. P0.09/P0.10 drive the etched NFC-A spiral. NEVER use
// as GPIO, never CONFIG_NFCT_PINS_AS_GPIOS (bootloader keeps USE_NFCT = yes).
#define PIN_NFC1             (9)    // P0.09 — NFC coil, never GPIO
#define PIN_NFC2             (10)   // P0.10 — NFC coil, never GPIO

#ifdef __cplusplus
}
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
